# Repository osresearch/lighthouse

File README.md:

Arduino (Teensy) and Processng library to interface with the HTC Vive
Lighthouse beacons.  Not fully functional yet.

More info: https://trmm.net/Lighthouse

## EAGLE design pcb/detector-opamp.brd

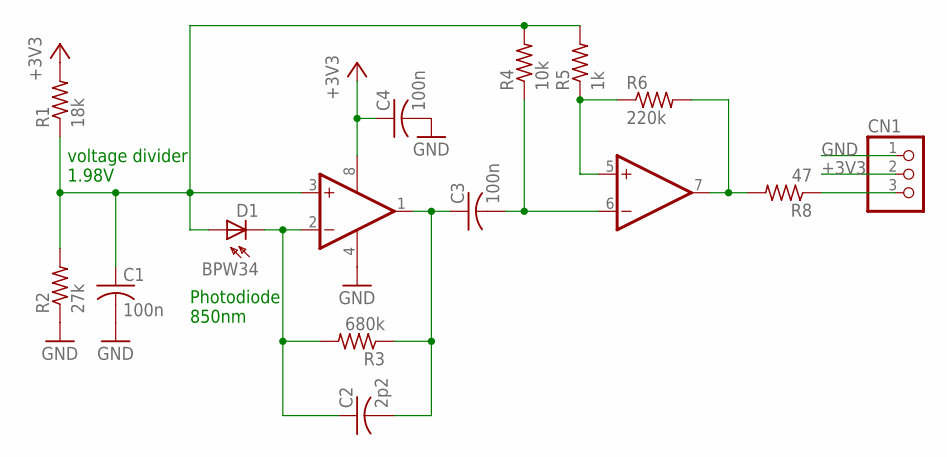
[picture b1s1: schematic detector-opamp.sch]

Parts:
C1, C3, C4: 100n; C0603K
C2: 2p2; C0603K
CN1: JST_3PIN; JSTPH3
D1: BPW34; BPW32
IC1: OPA2725D; SO08
R1: 18k; R0402
R2: 27k; R0402
R3: 680k; R0402
R4: 10k; R0402
R5: 1k; R0402
R6: 220k; R0402
R8: 47; R0402

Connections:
+3V3: C4.1, CN1.2, IC1.8 (V+), R1.2
GND: C1.2, C4.2, CN1.1, IC1.4 (V-), R2.1
unnamed: C1.1, D1.A, IC1.3 (+IN), R1.1, R2.2, R4.2, R5.2
unnamed: C2.2, C3.1, IC1.1 (OUT), R3.1
unnamed: C2.1, D1.K (C), IC1.2 (-IN), R3.2
unnamed: C3.2, IC1.6 (-IN), R4.1
unnamed: IC1.5 (+IN), R5.1, R6.1
unnamed: IC1.7 (OUT), R6.2, R8.2
unnamed: CN1.3, R8.1

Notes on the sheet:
voltage divider 1.98V
Photodiode 850nm

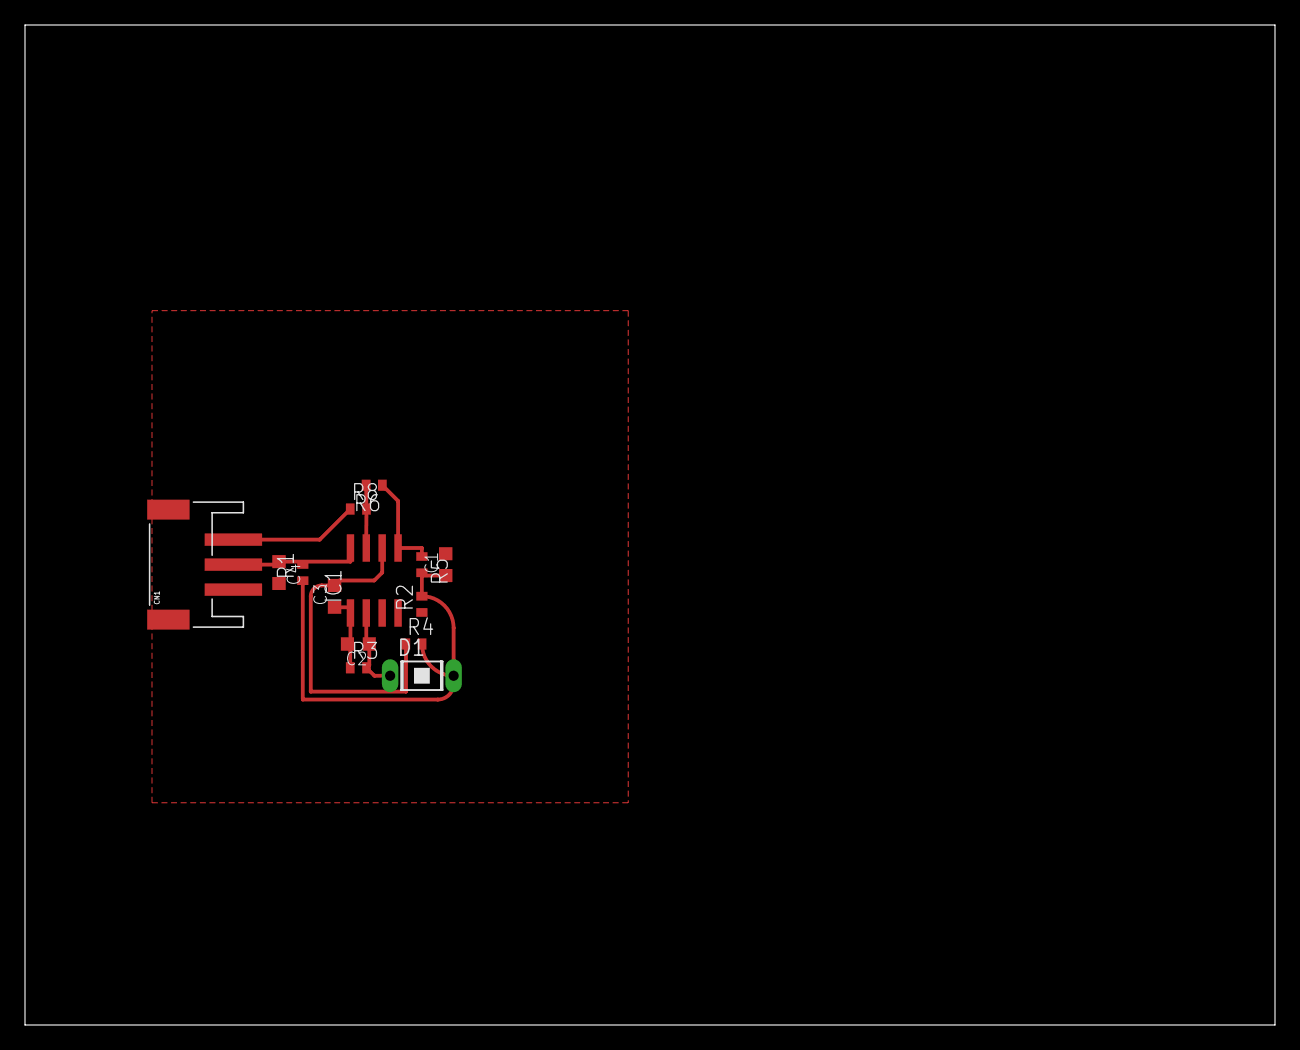
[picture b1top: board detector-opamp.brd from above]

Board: 2 copper layers, 100.0 x 80.0 mm, 14 parts (0 on the bottom side), 9 nets.

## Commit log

2016-06-21 import of code from old tree
2016-07-08 schematic reproduced from alan yates tweet
2016-07-09 Use input 5 on teensy 3 (prep for ICP)
2016-07-09 use the input capture function of the flexible timer module
2016-07-09 discrete photodiode amplifier
2016-07-09 switch pins and add debugging. seems to work with opamp
2016-07-10 circuit as built
2016-07-10 all four sensors work with the opamps
2016-07-10 remove debugging statements
2016-07-10 make private fields private again
2016-07-10 categorize the pulses into sync, sweep or other
2016-07-10 ignore generate files
2016-07-11 reorg slightly for clarity
2016-07-11 use other inputs
2016-07-11 more formatting tweaks
2016-12-03 Sync pulse decoding works.
    Use two inpute captures per sensor to get both pulse edges.
    Decode sync pulses to determine which sensor and axis.
2016-12-03 filtering the data works, all four sensors produce good data
2016-12-04 import of lighthouse computation from https://github.com/ashtuchkin/vive-diy-position-sensor
2016-12-04 Split Lighthouse code into objects.
    LighthouseSensor is the raw interface that computes the angles.
    LighthouseXYZ computes the position of a sensor given the angles.
2016-12-04 Split Lighthouse code into objects.
    LighthouseSensor is the raw interface that computes the angles.
    LighthouseXYZ computes the position of a sensor given the angles.
    Removed NED computation; leave things in the Lighthouse XYZ frame.
2016-12-04 output raw values for calibration
2016-12-04 attempt to numerically solve position of lighthouse from raw sensor readings
2016-12-05 compute the positions of the sensors in the lighthouse-centric reference frames
2016-12-05 forgot to square the distance; near perfect fit now
2016-12-05 use **2 to make the squaring clearer
2016-12-08 compute distances between sensors from the actual positions in sensor space
2016-12-09 read samples from stdin and average them
2016-12-13 started adding OOTX decoding, does not work yet
